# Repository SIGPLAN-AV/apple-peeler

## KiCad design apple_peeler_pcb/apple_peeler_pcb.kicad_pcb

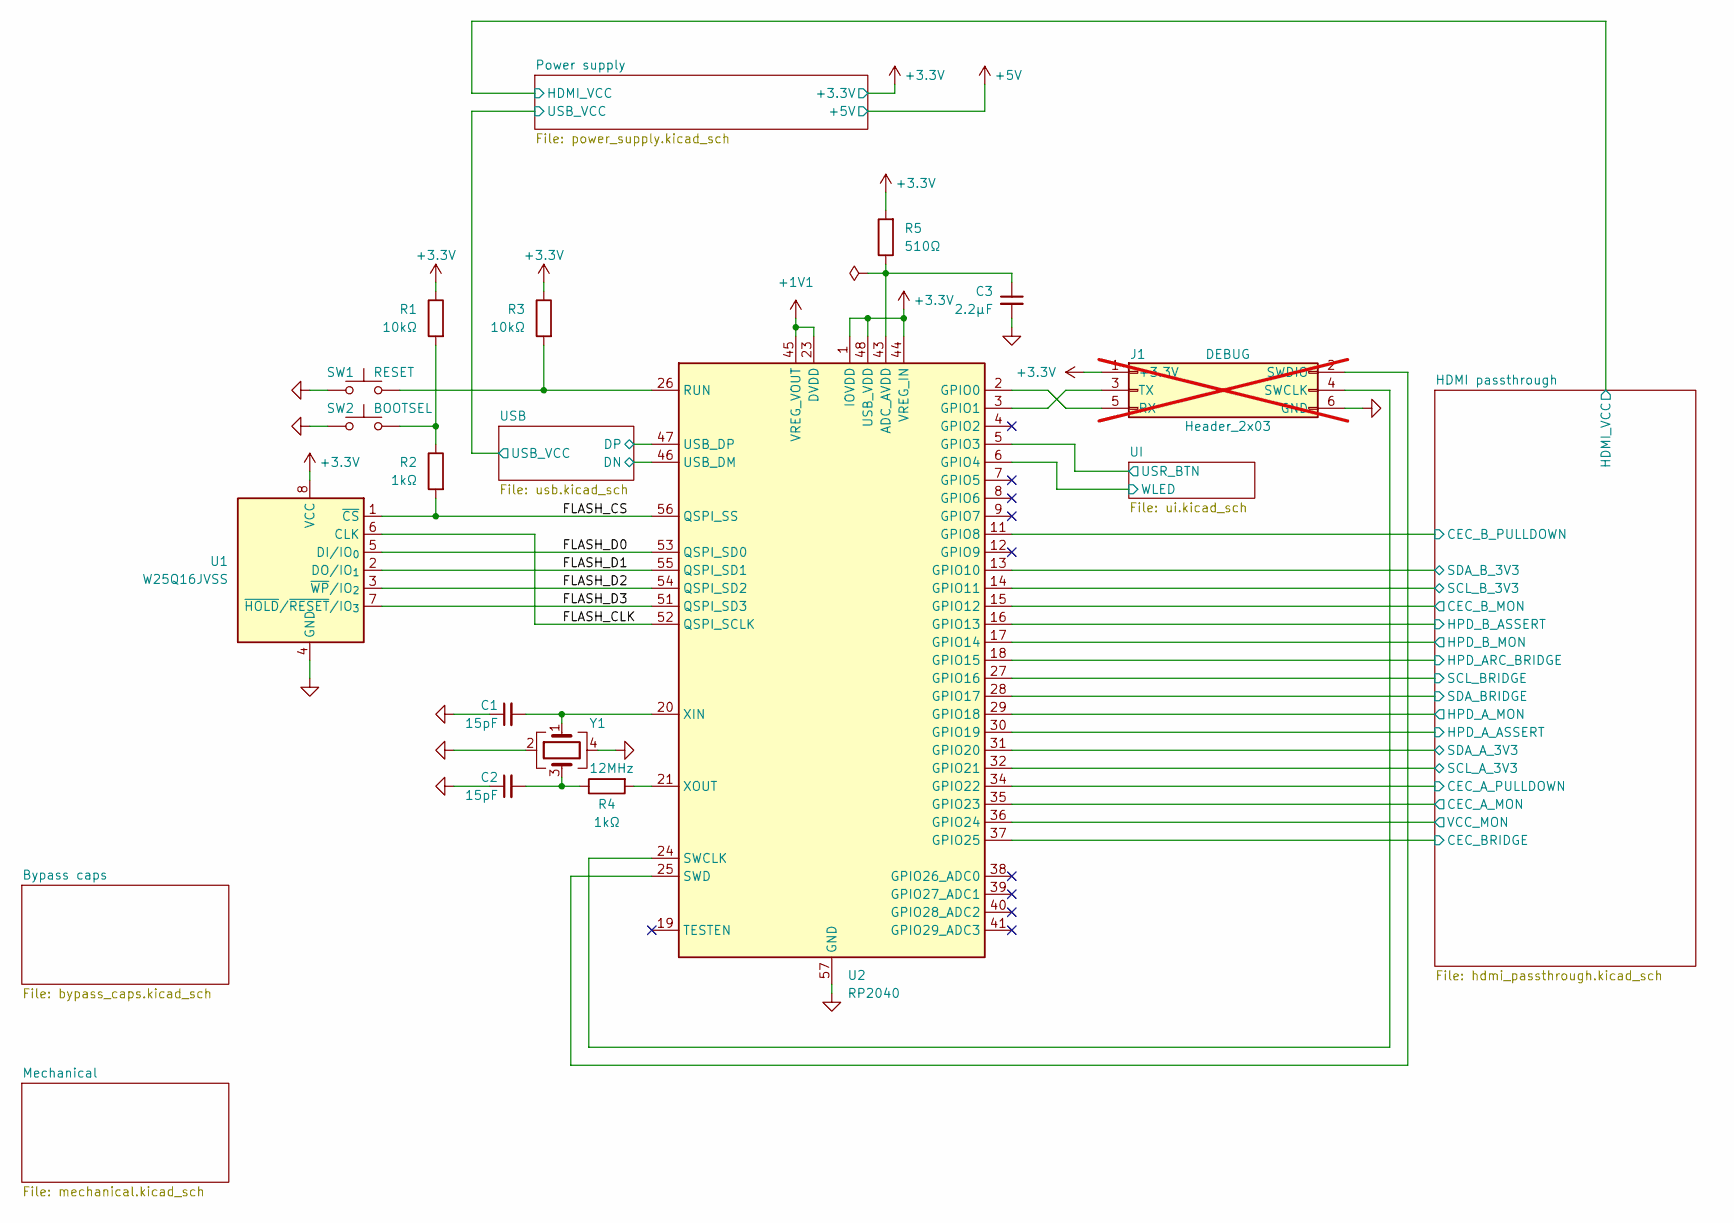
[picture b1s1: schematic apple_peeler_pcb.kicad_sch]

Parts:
C1, C2: 15pF; C_0805_2012Metric; MPN C 15pF 50V 0805; LCSC C107110
C3: 2.2μF; C_0805_2012Metric; MPN C 2.2μF 25V 0805; LCSC C377773
J1: Header_2x03; PinHeader_2x03_P2.54mm_Vertical; not fitted
R1, R3: 10kΩ; R_0805_2012Metric; MPN R 10kΩ 125mW 0805; LCSC C17414
R2, R4: 1kΩ; R_0805_2012Metric; MPN R 1kΩ 125mW 0805; LCSC C17513
R5: 510Ω; R_0805_2012Metric; MPN R 510Ω 125mW 0805; LCSC C17734
SW1, SW2: SPST BTN; SW_Push_1P1T_XKB_TS-1187A; MPN TS-1187A-B-A-B; LCSC C318884
U1: W25Q16JVSS; SOIC-8_5.3x5.3mm_P1.27mm; MPN W25Q16JVSSIQ; LCSC C131025
U2: RP2040; QFN-56-1EP_7x7mm_P0.4mm_EP3.2x3.2mm; MPN RP2040; LCSC C2040
Y1: 12MHz; Crystal_SMD_3225-4Pin_3.2x2.5mm; MPN X322512MSB4SI; LCSC C9002

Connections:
+1V1: U2.23 (DVDD), U2.45 (VREG_VOUT), U2.50 (DVDD); also elsewhere on the board
+3.3V: J1.1, R1.1, R3.1, R5.2, U1.8 (VCC), U2.1 (IOVDD), U2.10 (IOVDD), U2.22 (IOVDD), U2.33 (IOVDD), U2.42 (IOVDD), U2.44 (VREG_IN), U2.48 (USB_VDD), U2.49 (IOVDD); also elsewhere on the board
/FLASH_CLK: U1.6 (CLK), U2.52 (QSPI_SCLK)
/FLASH_CS: R2.2, U1.1 (~CS), U2.56 (QSPI_SS)
/FLASH_D0: U1.5 (DI/IO_{0}), U2.53 (QSPI_SD0)
/FLASH_D1: U1.2 (DO/IO_{1}), U2.55 (QSPI_SD1)
/FLASH_D2: U1.3 (~WP/IO_{2}), U2.54 (QSPI_SD2)
/FLASH_D3: U1.7 (~HOLD/~RESET/IO_{3}), U2.51 (QSPI_SD3)
/HDMI passthrough/CEC_A_MON: U2.35 (GPIO23); also elsewhere on the board
/HDMI passthrough/CEC_A_PULLDOWN: U2.34 (GPIO22); also elsewhere on the board
/HDMI passthrough/CEC_BRIDGE: U2.37 (GPIO25); also elsewhere on the board
/HDMI passthrough/CEC_B_MON: U2.15 (GPIO12); also elsewhere on the board
/HDMI passthrough/CEC_B_PULLDOWN: U2.11 (GPIO8); also elsewhere on the board
/HDMI passthrough/HPD_ARC_BRIDGE: U2.18 (GPIO15); also elsewhere on the board
/HDMI passthrough/HPD_A_ASSERT: U2.30 (GPIO19); also elsewhere on the board
/HDMI passthrough/HPD_A_MON: U2.29 (GPIO18); also elsewhere on the board
/HDMI passthrough/HPD_B_ASSERT: U2.16 (GPIO13); also elsewhere on the board
/HDMI passthrough/HPD_B_MON: U2.17 (GPIO14); also elsewhere on the board
/HDMI passthrough/SCL_A_3V3: U2.32 (GPIO21); also elsewhere on the board
/HDMI passthrough/SCL_BRIDGE: U2.27 (GPIO16); also elsewhere on the board
/HDMI passthrough/SCL_B_3V3: U2.14 (GPIO11); also elsewhere on the board
/HDMI passthrough/SDA_A_3V3: U2.31 (GPIO20); also elsewhere on the board
/HDMI passthrough/SDA_BRIDGE: U2.28 (GPIO17); also elsewhere on the board
/HDMI passthrough/SDA_B_3V3: U2.13 (GPIO10); also elsewhere on the board
/HDMI passthrough/VCC_MON: U2.36 (GPIO24); also elsewhere on the board
/UI/USR_BTN: U2.5 (GPIO3); also elsewhere on the board
/UI/WLED: U2.6 (GPIO4); also elsewhere on the board
/USB/DN: U2.46 (USB_DM); also elsewhere on the board
/USB/DP: U2.47 (USB_DP); also elsewhere on the board
GND: C1.1, C2.1, C3.2, J1.6, SW1.1, SW2.1, U1.4 (GND), U2.57 (GND), Y1.2, Y1.4; also elsewhere on the board
unnamed: C2.2, R4.1, Y1.3
unnamed: J1.2, U2.25 (SWD)
unnamed: J1.3, U2.3 (GPIO1)
unnamed: J1.4, U2.24 (SWCLK)
unnamed: J1.5, U2.2 (GPIO0)
unnamed: R1.2, R2.1, SW2.2
unnamed: C3.1, R5.1, U2.43 (ADC_AVDD)
unnamed: R3.2, SW1.2, U2.26 (RUN)
unnamed: C1.2, U2.20 (XIN), Y1.1
unnamed: R4.2, U2.21 (XOUT)

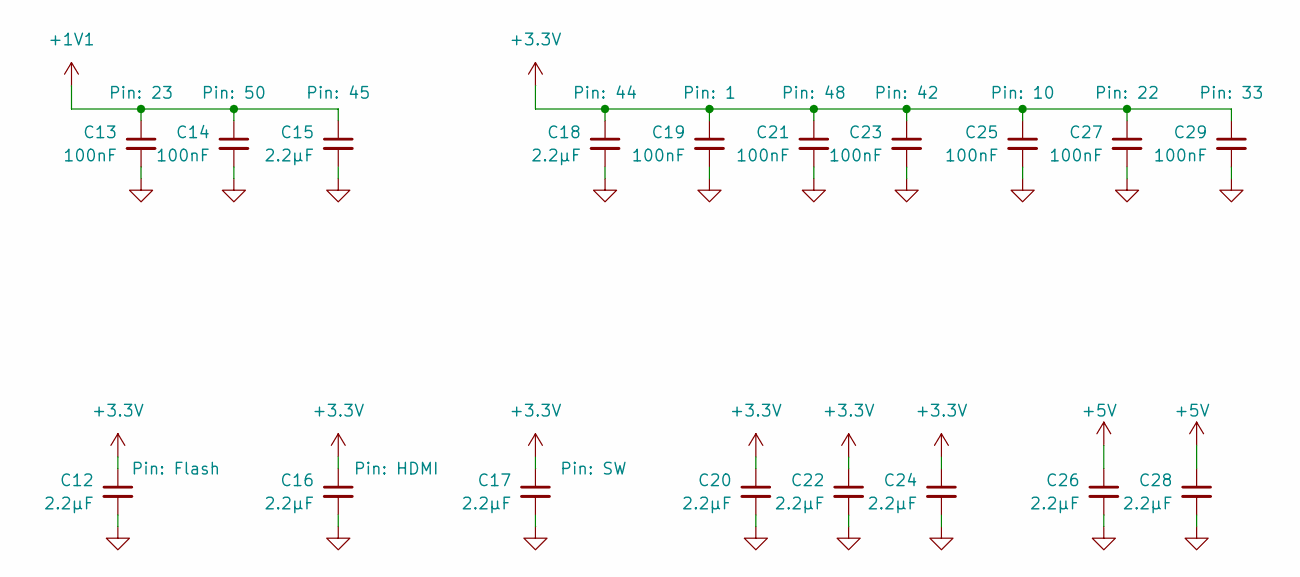
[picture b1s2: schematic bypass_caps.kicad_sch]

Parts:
C12, C15, C16, C17, C18, C20, C22, C24, C26, C28: 2.2μF; C_0805_2012Metric; MPN C 2.2μF 25V 0805; LCSC C377773
C13, C14, C19, C21, C23, C25, C27, C29: 100nF; C_0805_2012Metric; MPN C 100nF 50V 0805; LCSC C49678

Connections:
+1V1: C13.1, C14.1, C15.1; also elsewhere on the board
+3.3V: C12.1, C16.1, C17.1, C18.1, C19.1, C20.1, C21.1, C22.1, C23.1, C24.1, C25.1, C27.1, C29.1; also elsewhere on the board
+5V: C26.1, C28.1; also elsewhere on the board
GND: C12.2, C13.2, C14.2, C15.2, C16.2, C17.2, C18.2, C19.2, C20.2, C21.2, C22.2, C23.2, C24.2, C25.2, C26.2, C27.2, C28.2, C29.2; also elsewhere on the board

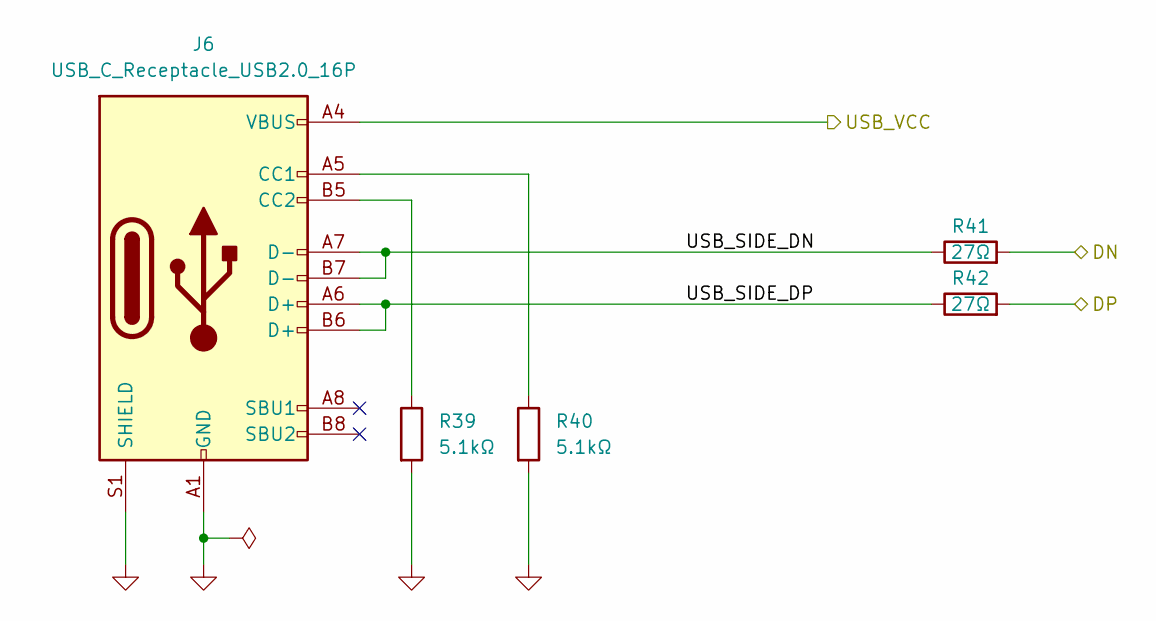
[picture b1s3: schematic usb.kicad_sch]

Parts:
J6: USB_C_Receptacle_USB2.0_16P; USB_C_Receptacle_G-Switch_GT-USB-7010ASV; MPN TYPE-C 16PIN 2MD(073); LCSC C2765186
R39, R40: 5.1kΩ; R_0805_2012Metric; MPN R 5.1kΩ 125mW 0805; LCSC C27834
R41, R42: 27Ω; R_0805_2012Metric; MPN R 27Ω 125mW 0805; LCSC C17594

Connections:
/Power supply/USB_VCC: J6.A4 (VBUS), J6.A9 (VBUS), J6.B4 (VBUS), J6.B9 (VBUS); also elsewhere on the board
/USB/DN: R41.2; also elsewhere on the board
/USB/DP: R42.2; also elsewhere on the board
/USB/USB_SIDE_DN: J6.A7 (D-), J6.B7 (D-), R41.1
/USB/USB_SIDE_DP: J6.A6 (D+), J6.B6 (D+), R42.1
GND: J6.A1 (GND), J6.A12 (GND), J6.B1 (GND), J6.B12 (GND), J6.S1 (SHIELD), R39.2, R40.2; also elsewhere on the board
unnamed: J6.A5 (CC1), R40.1
unnamed: J6.B5 (CC2), R39.1

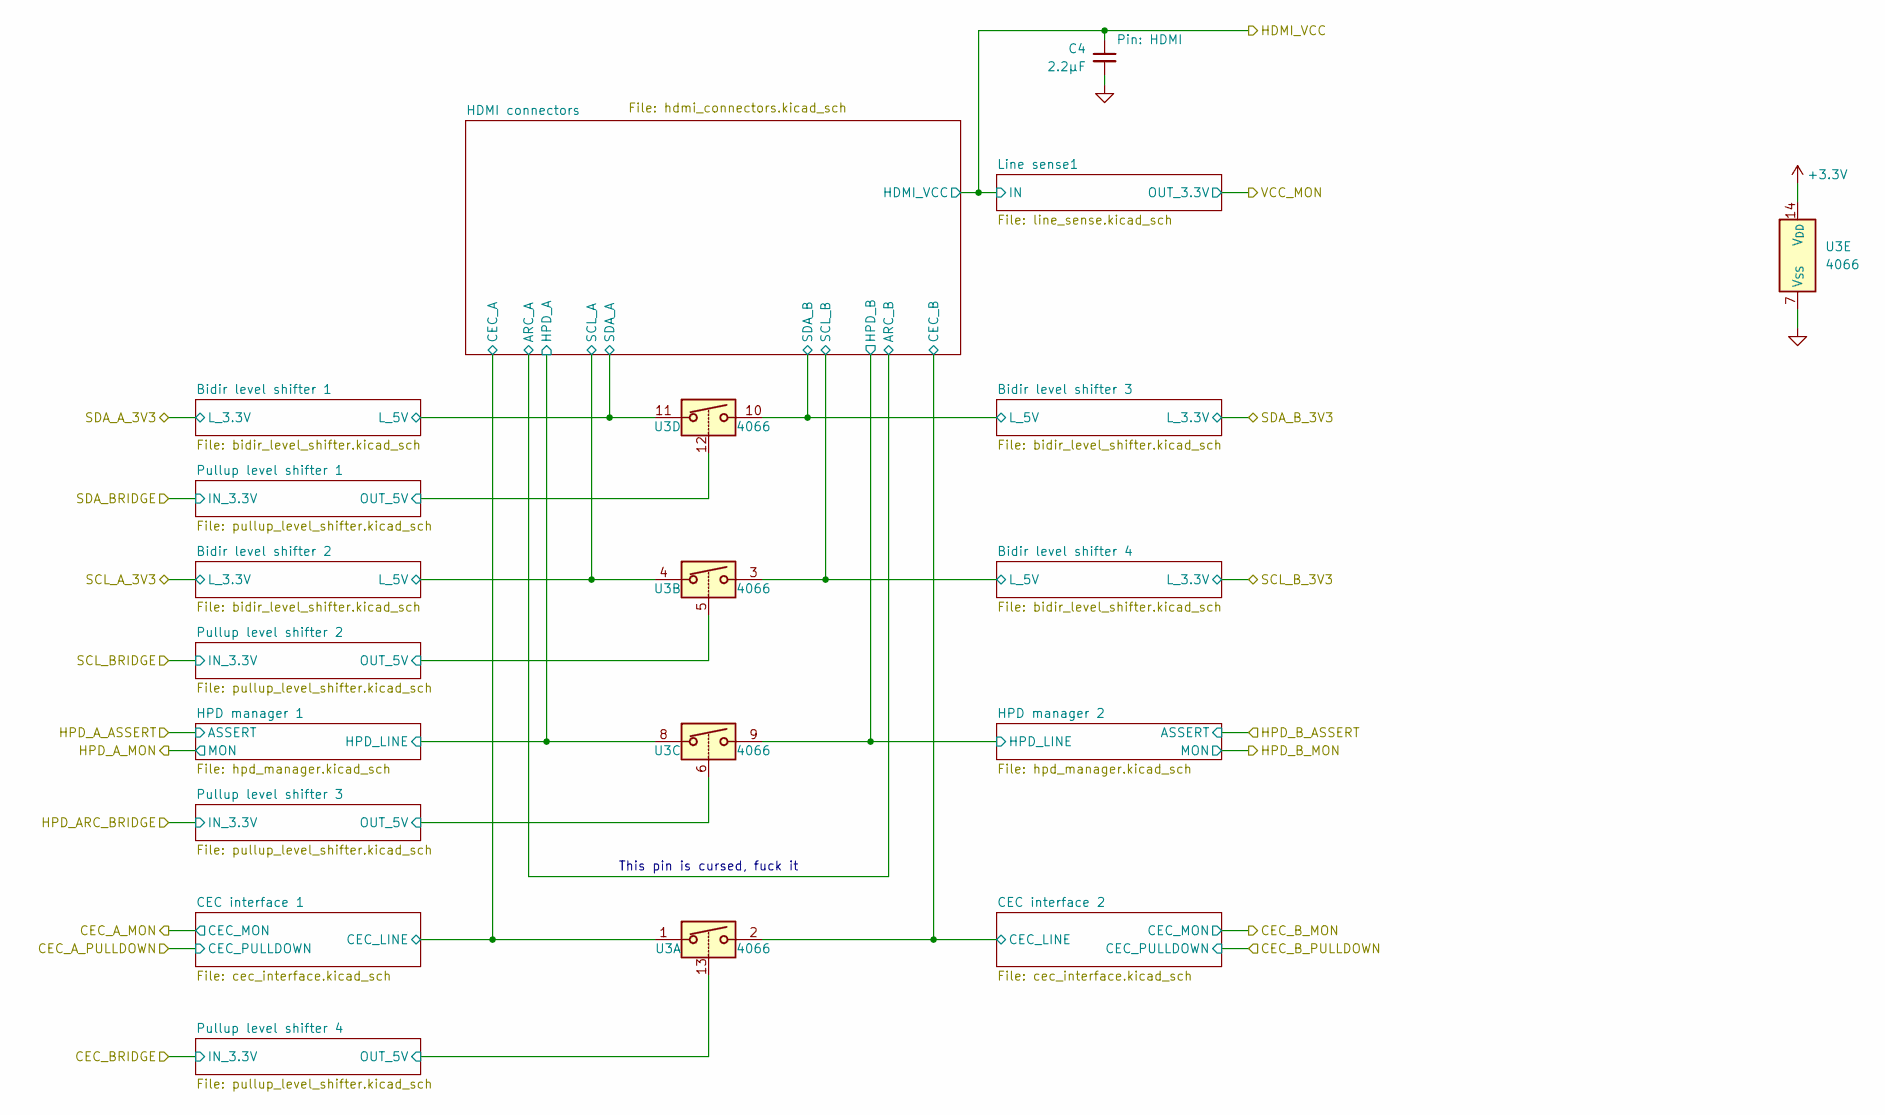
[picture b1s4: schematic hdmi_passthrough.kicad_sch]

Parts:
C4: 2.2μF; C_0805_2012Metric; MPN C 2.2μF 25V 0805; LCSC C377773
U3: 4066; SO-14_3.9x8.65mm_P1.27mm; MPN CD4066BM/TR; LCSC C512770

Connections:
+3.3V: U3.14 (V_{DD}); also elsewhere on the board
/HDMI passthrough/Bidir level shifter 1/L_5V: U3.11; also elsewhere on the board
/HDMI passthrough/Bidir level shifter 2/L_5V: U3.4; also elsewhere on the board
/HDMI passthrough/Bidir level shifter 3/L_5V: U3.10; also elsewhere on the board
/HDMI passthrough/Bidir level shifter 4/L_5V: U3.3; also elsewhere on the board
/HDMI passthrough/CEC interface 1/CEC_LINE: U3.1; also elsewhere on the board
/HDMI passthrough/CEC interface 2/CEC_LINE: U3.2; also elsewhere on the board
/HDMI passthrough/HDMI connectors/HPD_A: U3.8; also elsewhere on the board
/HDMI passthrough/HDMI connectors/HPD_B: U3.9; also elsewhere on the board
/HDMI passthrough/HDMI_VCC: C4.1; also elsewhere on the board
/HDMI passthrough/Pullup level shifter 1/OUT_5V: U3.12; also elsewhere on the board
/HDMI passthrough/Pullup level shifter 2/OUT_5V: U3.5; also elsewhere on the board
/HDMI passthrough/Pullup level shifter 3/OUT_5V: U3.6; also elsewhere on the board
/HDMI passthrough/Pullup level shifter 4/OUT_5V: U3.13; also elsewhere on the board
GND: C4.2, U3.7 (V_{SS}); also elsewhere on the board

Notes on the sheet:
This pin is cursed, fuck it

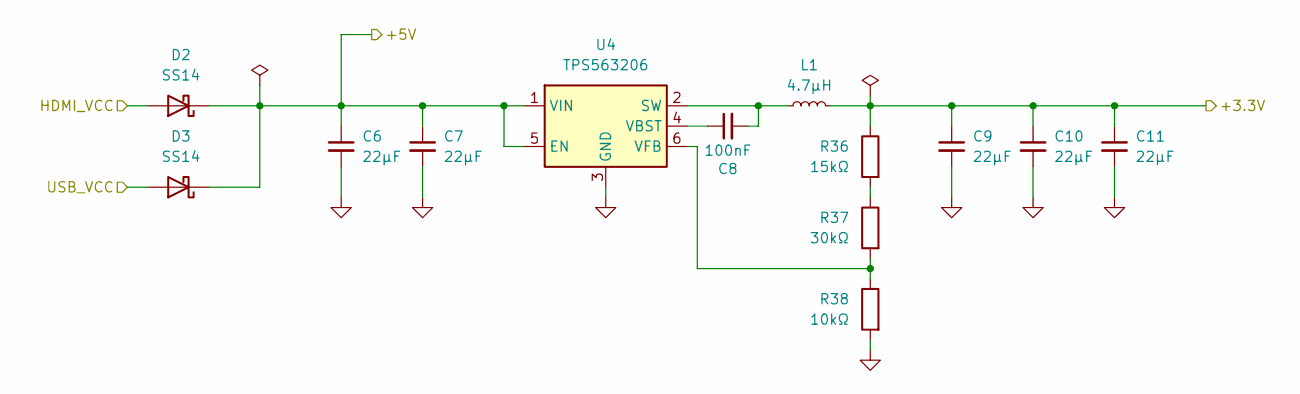
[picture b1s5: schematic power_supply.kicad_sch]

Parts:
C6, C7, C9, C10, C11: 22μF; C_0805_2012Metric; MPN C 22μF 25V 0805; LCSC C45783
C8: 100nF; C_0805_2012Metric; MPN C 100nF 50V 0805; LCSC C49678
D2, D3: SS14; D_SMA; MPN SS14; LCSC C2480
L1: 4.7μH; L_Sunlord_SWPA5020S; MPN SWPA5020S4R7MT; LCSC C43183
R36: 15kΩ; R_0805_2012Metric; MPN R 15kΩ 125mW 0805; LCSC C17475
R37: 30kΩ; R_0805_2012Metric; MPN R 30kΩ 125mW 0805; LCSC C17621
R38: 10kΩ; R_0805_2012Metric; MPN R 10kΩ 125mW 0805; LCSC C17414
U4: TPS563206; SOT-563; MPN TPS563206DRLR; LCSC C22427434

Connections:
+3.3V: C9.1, C10.1, C11.1, L1.2, R36.1; also elsewhere on the board
+5V: C6.1, C7.1, D2.1 (K), D3.1 (K), U4.1 (VIN), U4.5 (EN); also elsewhere on the board
/HDMI passthrough/HDMI_VCC: D2.2 (A); also elsewhere on the board
/Power supply/USB_VCC: D3.2 (A); also elsewhere on the board
GND: C6.2, C7.2, C9.2, C10.2, C11.2, R38.2, U4.3 (GND); also elsewhere on the board
unnamed: R36.2, R37.1
unnamed: C8.2, L1.1, U4.2 (SW)
unnamed: C8.1, U4.4 (VBST)
unnamed: R37.2, R38.1, U4.6 (VFB)

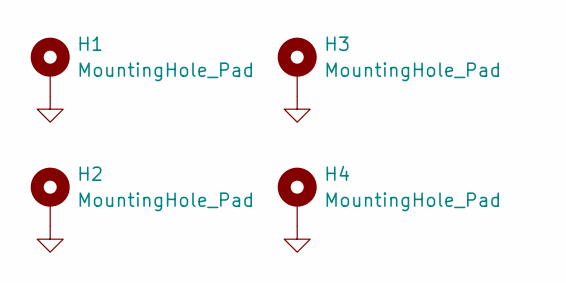
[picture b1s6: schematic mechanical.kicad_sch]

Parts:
H1, H2, H3, H4: MountingHole_Pad; MountingHole_3.2mm_M3_Pad_Via

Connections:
GND: H1.1, H2.1, H3.1, H4.1; also elsewhere on the board

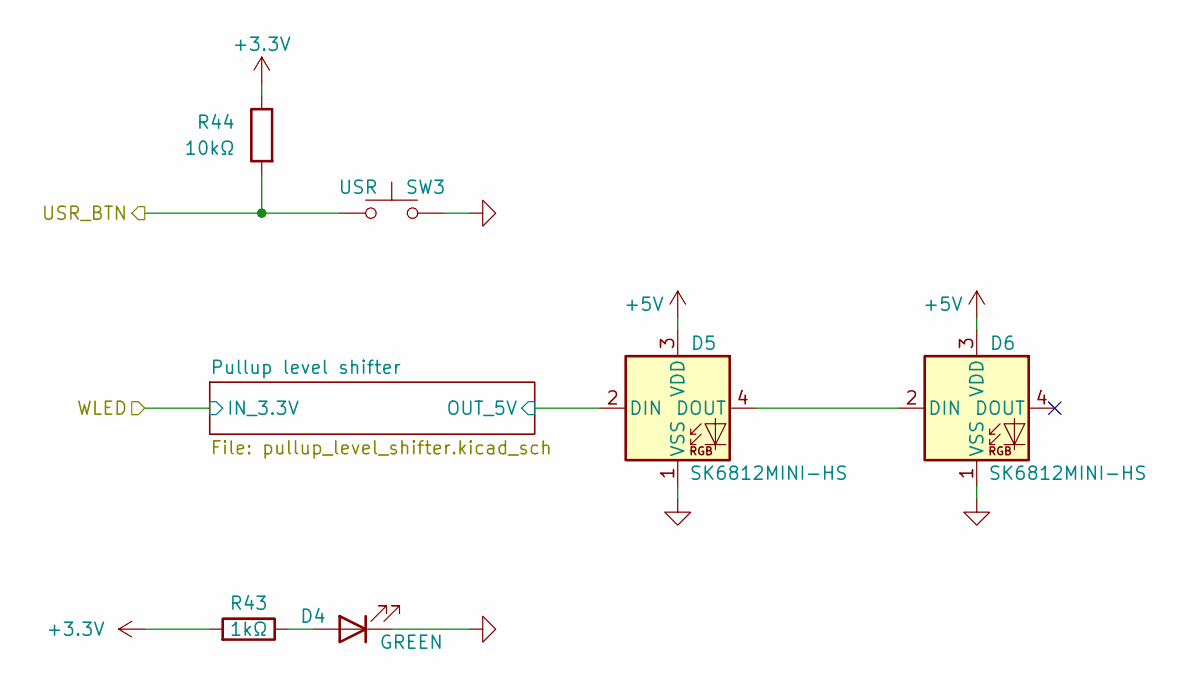
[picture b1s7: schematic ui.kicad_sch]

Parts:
D4: GREEN; LED_0805_2012Metric; MPN KT-0805G; LCSC C2297
D5, D6: SK6812MINI-HS; LED_SK6812MINI_HS_012; MPN SK6812MINI-HS; LCSC C2922787
R43: 1kΩ; R_0805_2012Metric; MPN R 1kΩ 125mW 0805; LCSC C17513
R44: 10kΩ; R_0805_2012Metric; MPN R 10kΩ 125mW 0805; LCSC C17414
SW3: SPST BTN; SW_Push_1P1T_XKB_TS-1187A; MPN TS-1187A-B-A-B; LCSC C318884

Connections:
+3.3V: R43.2, R44.1; also elsewhere on the board
+5V: D5.3 (VDD), D6.3 (VDD); also elsewhere on the board
/UI/Pullup level shifter/OUT_5V: D5.2 (DIN); also elsewhere on the board
/UI/USR_BTN: R44.2, SW3.2; also elsewhere on the board
GND: D4.1 (K), D5.1 (VSS), D6.1 (VSS), SW3.1; also elsewhere on the board
unnamed: D4.2 (A), R43.1
unnamed: D5.4 (DOUT), D6.2 (DIN)

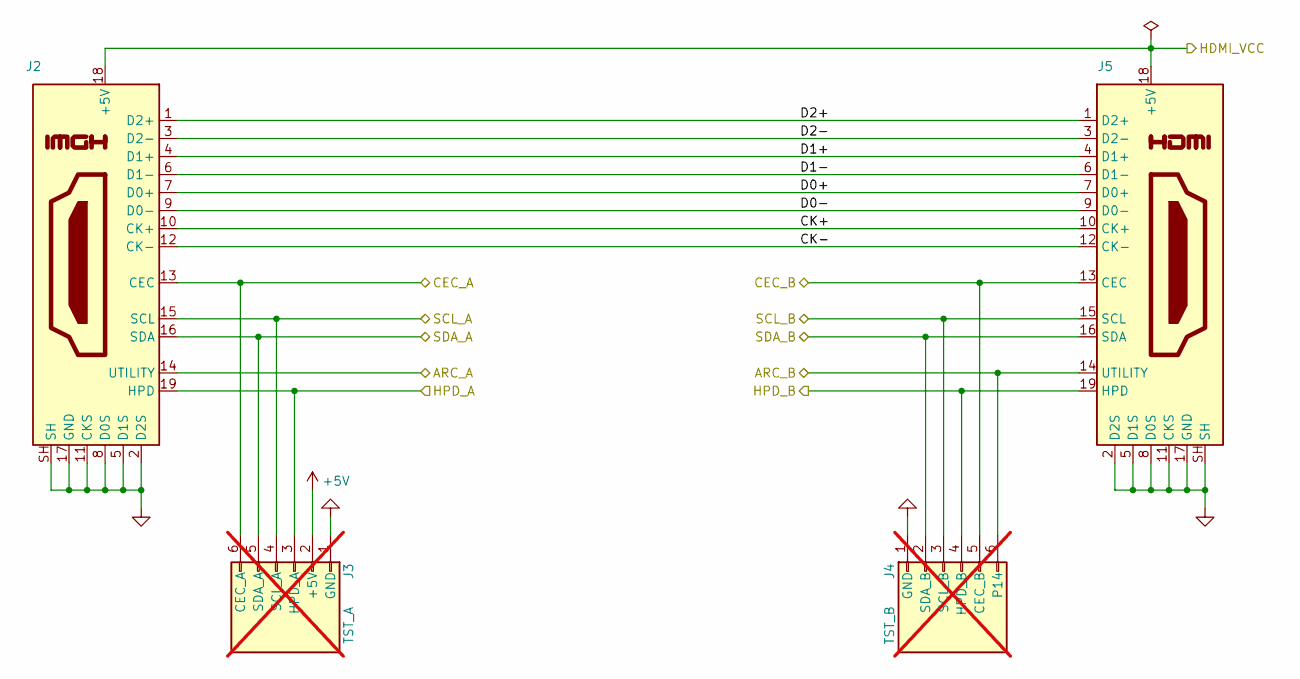
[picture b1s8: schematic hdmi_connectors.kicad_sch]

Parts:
J2, J5: HDMI-001 19PCBTP; HDMI_A_Molex_208658-1001_Horizontal; MPN Molex_208658; LCSC C138388
J3, J4: Header_01x06; PinHeader_1x06_P2.54mm_Vertical; MPN Header_01x06; not fitted

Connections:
+5V: J3.2; also elsewhere on the board
/HDMI passthrough/Bidir level shifter 1/L_5V: J2.16 (SDA), J3.5; also elsewhere on the board
/HDMI passthrough/Bidir level shifter 2/L_5V: J2.15 (SCL), J3.4; also elsewhere on the board
/HDMI passthrough/Bidir level shifter 3/L_5V: J4.2, J5.16 (SDA); also elsewhere on the board
/HDMI passthrough/Bidir level shifter 4/L_5V: J4.3, J5.15 (SCL); also elsewhere on the board
/HDMI passthrough/CEC interface 1/CEC_LINE: J2.13 (CEC), J3.6; also elsewhere on the board
/HDMI passthrough/CEC interface 2/CEC_LINE: J4.5, J5.13 (CEC); also elsewhere on the board
/HDMI passthrough/HDMI connectors/ARC_A: J2.14 (UTILITY), J4.6, J5.14 (UTILITY)
/HDMI passthrough/HDMI connectors/CK+: J2.10 (CK+), J5.10 (CK+)
/HDMI passthrough/HDMI connectors/CK-: J2.12 (CK-), J5.12 (CK-)
/HDMI passthrough/HDMI connectors/D0+: J2.7 (D0+), J5.7 (D0+)
/HDMI passthrough/HDMI connectors/D0-: J2.9 (D0-), J5.9 (D0-)
/HDMI passthrough/HDMI connectors/D1+: J2.4 (D1+), J5.4 (D1+)
/HDMI passthrough/HDMI connectors/D1-: J2.6 (D1-), J5.6 (D1-)
/HDMI passthrough/HDMI connectors/D2+: J2.1 (D2+), J5.1 (D2+)
/HDMI passthrough/HDMI connectors/D2-: J2.3 (D2-), J5.3 (D2-)
/HDMI passthrough/HDMI connectors/HPD_A: J2.19 (HPD), J3.3; also elsewhere on the board
/HDMI passthrough/HDMI connectors/HPD_B: J4.4, J5.19 (HPD); also elsewhere on the board
/HDMI passthrough/HDMI_VCC: J2.18 (+5V), J5.18 (+5V); also elsewhere on the board
GND: J2.2 (D2S), J2.5 (D1S), J2.8 (D0S), J2.11 (CKS), J2.17 (GND), J2.SH, J3.1, J4.1, J5.2 (D2S), J5.5 (D1S), J5.8 (D0S), J5.11 (CKS), J5.17 (GND), J5.SH; also elsewhere on the board

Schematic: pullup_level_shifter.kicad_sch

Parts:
Q5: 2N7002; SOT-23; MPN 2N7002; LCSC C8545
R14: 510Ω; R_0805_2012Metric; MPN R 510Ω 125mW 0805; LCSC C17734
R15: 470kΩ; R_0805_2012Metric; MPN R 470kΩ 125mW 0805; LCSC C17709
R16: 10kΩ; R_0805_2012Metric; MPN R 10kΩ 125mW 0805; LCSC C17414

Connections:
+5V: R16.1; also elsewhere on the board
/HDMI passthrough/Pullup level shifter 1/OUT_5V: Q5.3 (D), R16.2; also elsewhere on the board
/HDMI passthrough/SDA_BRIDGE: R14.1; also elsewhere on the board
GND: Q5.2 (S), R15.2; also elsewhere on the board
unnamed: Q5.1 (G), R14.2, R15.1

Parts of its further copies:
Q6, Q7, Q10, Q18: 2N7002; SOT-23; MPN 2N7002; LCSC C8545
R17, R20, R29, R62: 510Ω; R_0805_2012Metric; MPN R 510Ω 125mW 0805; LCSC C17734
R18, R21, R30, R63: 470kΩ; R_0805_2012Metric; MPN R 470kΩ 125mW 0805; LCSC C17709
R19, R22, R31, R64: 10kΩ; R_0805_2012Metric; MPN R 10kΩ 125mW 0805; LCSC C17414

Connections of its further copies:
+5V: R19.1, R22.1, R31.1, R64.1; also elsewhere on the board
/HDMI passthrough/CEC_BRIDGE: R29.1; also elsewhere on the board
/HDMI passthrough/HPD_ARC_BRIDGE: R20.1; also elsewhere on the board
/HDMI passthrough/Pullup level shifter 2/OUT_5V: Q6.3 (D), R19.2; also elsewhere on the board
/HDMI passthrough/Pullup level shifter 3/OUT_5V: Q7.3 (D), R22.2; also elsewhere on the board
/HDMI passthrough/Pullup level shifter 4/OUT_5V: Q10.3 (D), R31.2; also elsewhere on the board
/HDMI passthrough/SCL_BRIDGE: R17.1; also elsewhere on the board
/UI/Pullup level shifter/OUT_5V: Q18.3 (D), R64.2; also elsewhere on the board
/UI/WLED: R62.1; also elsewhere on the board
GND: Q6.2 (S), Q7.2 (S), Q10.2 (S), Q18.2 (S), R18.2, R21.2, R30.2, R63.2; also elsewhere on the board
unnamed: Q6.1 (G), R17.2, R18.1
unnamed: Q7.1 (G), R20.2, R21.1
unnamed: Q10.1 (G), R29.2, R30.1
unnamed: Q18.1 (G), R62.2, R63.1

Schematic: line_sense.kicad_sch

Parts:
Q8: 2N7002; SOT-23; MPN 2N7002; LCSC C8545
R23: 510Ω; R_0805_2012Metric; MPN R 510Ω 125mW 0805; LCSC C17734
R24: 470kΩ; R_0805_2012Metric; MPN R 470kΩ 125mW 0805; LCSC C17709
R25: 10kΩ; R_0805_2012Metric; MPN R 10kΩ 125mW 0805; LCSC C17414

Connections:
+3.3V: R25.1; also elsewhere on the board
/HDMI passthrough/HDMI connectors/HPD_B: R23.1; also elsewhere on the board
/HDMI passthrough/HPD_B_MON: Q8.3 (D), R25.2; also elsewhere on the board
GND: Q8.2 (S), R24.2; also elsewhere on the board
unnamed: Q8.1 (G), R23.2, R24.1

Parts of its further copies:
Q9, Q12: 2N7002; SOT-23; MPN 2N7002; LCSC C8545
R26, R45: 510Ω; R_0805_2012Metric; MPN R 510Ω 125mW 0805; LCSC C17734
R27, R46: 470kΩ; R_0805_2012Metric; MPN R 470kΩ 125mW 0805; LCSC C17709
R28, R47: 10kΩ; R_0805_2012Metric; MPN R 10kΩ 125mW 0805; LCSC C17414

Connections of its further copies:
+3.3V: R28.1, R47.1; also elsewhere on the board
/HDMI passthrough/HDMI connectors/HPD_A: R45.1; also elsewhere on the board
/HDMI passthrough/HDMI_VCC: R26.1; also elsewhere on the board
/HDMI passthrough/HPD_A_MON: Q12.3 (D), R47.2; also elsewhere on the board
/HDMI passthrough/VCC_MON: Q9.3 (D), R28.2; also elsewhere on the board
GND: Q9.2 (S), Q12.2 (S), R27.2, R46.2; also elsewhere on the board
unnamed: Q9.1 (G), R26.2, R27.1
unnamed: Q12.1 (G), R45.2, R46.1

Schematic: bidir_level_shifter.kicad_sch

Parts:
Q1: 2N7002; SOT-23; MPN 2N7002; LCSC C8545
R6, R7: 10kΩ; R_0805_2012Metric; MPN R 10kΩ 125mW 0805; LCSC C17414

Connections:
+3.3V: Q1.1 (G), R6.1; also elsewhere on the board
+5V: R7.1; also elsewhere on the board
/HDMI passthrough/Bidir level shifter 1/L_5V: Q1.3 (D), R7.2; also elsewhere on the board
/HDMI passthrough/SDA_A_3V3: Q1.2 (S), R6.2; also elsewhere on the board

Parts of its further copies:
Q2, Q3, Q4: 2N7002; SOT-23; MPN 2N7002; LCSC C8545
R8, R9, R10, R11, R12, R13: 10kΩ; R_0805_2012Metric; MPN R 10kΩ 125mW 0805; LCSC C17414

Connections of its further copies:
+3.3V: Q2.1 (G), Q3.1 (G), Q4.1 (G), R8.1, R10.1, R12.1; also elsewhere on the board
+5V: R9.1, R11.1, R13.1; also elsewhere on the board
/HDMI passthrough/Bidir level shifter 2/L_5V: Q2.3 (D), R9.2; also elsewhere on the board
/HDMI passthrough/Bidir level shifter 3/L_5V: Q3.3 (D), R11.2; also elsewhere on the board
/HDMI passthrough/Bidir level shifter 4/L_5V: Q4.3 (D), R13.2; also elsewhere on the board
/HDMI passthrough/SCL_A_3V3: Q2.2 (S), R8.2; also elsewhere on the board
/HDMI passthrough/SCL_B_3V3: Q4.2 (S), R12.2; also elsewhere on the board
/HDMI passthrough/SDA_B_3V3: Q3.2 (S), R10.2; also elsewhere on the board

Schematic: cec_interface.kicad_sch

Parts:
C5: 100pF; C_0805_2012Metric; MPN C 100pF 50V 0805; LCSC C1790
D1: 1N4148WS; D_SOD-323; MPN 1N4148WS; LCSC C2128
Q11: 2N7002; SOT-23; MPN 2N7002; LCSC C8545
R32: 510Ω; R_0805_2012Metric; MPN R 510Ω 125mW 0805; LCSC C17734
R33: 470kΩ; R_0805_2012Metric; MPN R 470kΩ 125mW 0805; LCSC C17709
R34: 27kΩ; R_0805_2012Metric; MPN R 27kΩ 125mW 0805; LCSC C17593
R35: 47kΩ; R_0805_2012Metric; MPN R 47kΩ 125mW 0805; LCSC C17713

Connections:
+3.3V: R34.1; also elsewhere on the board
/HDMI passthrough/CEC interface 1/CEC_LINE: D1.1 (K), Q11.3 (D); also elsewhere on the board
/HDMI passthrough/CEC_A_MON: C5.1, R35.2; also elsewhere on the board
/HDMI passthrough/CEC_A_PULLDOWN: R32.1; also elsewhere on the board
GND: C5.2, Q11.2 (S), R33.2; also elsewhere on the board
unnamed: D1.2 (A), R34.2, R35.1
unnamed: Q11.1 (G), R32.2, R33.1

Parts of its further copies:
C30: 100pF; C_0805_2012Metric; MPN C 100pF 50V 0805; LCSC C1790
D7: 1N4148WS; D_SOD-323; MPN 1N4148WS; LCSC C2128
Q17: 2N7002; SOT-23; MPN 2N7002; LCSC C8545
R58: 510Ω; R_0805_2012Metric; MPN R 510Ω 125mW 0805; LCSC C17734
R59: 470kΩ; R_0805_2012Metric; MPN R 470kΩ 125mW 0805; LCSC C17709
R60: 27kΩ; R_0805_2012Metric; MPN R 27kΩ 125mW 0805; LCSC C17593
R61: 47kΩ; R_0805_2012Metric; MPN R 47kΩ 125mW 0805; LCSC C17713

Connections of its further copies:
+3.3V: R60.1; also elsewhere on the board
/HDMI passthrough/CEC interface 2/CEC_LINE: D7.1 (K), Q17.3 (D); also elsewhere on the board
/HDMI passthrough/CEC_B_MON: C30.1, R61.2; also elsewhere on the board
/HDMI passthrough/CEC_B_PULLDOWN: R58.1; also elsewhere on the board
GND: C30.2, Q17.2 (S), R59.2; also elsewhere on the board
unnamed: D7.2 (A), R60.2, R61.1
unnamed: Q17.1 (G), R58.2, R59.1

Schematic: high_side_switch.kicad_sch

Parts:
Q13: 2N7002; SOT-23; MPN 2N7002; LCSC C8545
Q14: AO3401A; SOT-23; MPN AO3401A; LCSC C15127
R48, R51: 510Ω; R_0805_2012Metric; MPN R 510Ω 125mW 0805; LCSC C17734
R49, R52: 470kΩ; R_0805_2012Metric; MPN R 470kΩ 125mW 0805; LCSC C17709
R50: 10kΩ; R_0805_2012Metric; MPN R 10kΩ 125mW 0805; LCSC C17414

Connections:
+5V: Q14.2 (S), R50.1; also elsewhere on the board
/HDMI passthrough/HDMI connectors/HPD_A: Q14.3 (D), R52.1; also elsewhere on the board
/HDMI passthrough/HPD_A_ASSERT: R48.1; also elsewhere on the board
GND: Q13.2 (S), R49.2, R52.2; also elsewhere on the board
unnamed: Q13.3 (D), R51.2
unnamed: Q13.1 (G), R48.2, R49.1
unnamed: Q14.1 (G), R50.2, R51.1

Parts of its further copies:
Q15: 2N7002; SOT-23; MPN 2N7002; LCSC C8545
Q16: AO3401A; SOT-23; MPN AO3401A; LCSC C15127
R53, R56: 510Ω; R_0805_2012Metric; MPN R 510Ω 125mW 0805; LCSC C17734
R54, R57: 470kΩ; R_0805_2012Metric; MPN R 470kΩ 125mW 0805; LCSC C17709
R55: 10kΩ; R_0805_2012Metric; MPN R 10kΩ 125mW 0805; LCSC C17414

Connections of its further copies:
+5V: Q16.2 (S), R55.1; also elsewhere on the board
/HDMI passthrough/HDMI connectors/HPD_B: Q16.3 (D), R57.1; also elsewhere on the board
/HDMI passthrough/HPD_B_ASSERT: R53.1; also elsewhere on the board
GND: Q15.2 (S), R54.2, R57.2; also elsewhere on the board
unnamed: Q15.3 (D), R56.2
unnamed: Q15.1 (G), R53.2, R54.1
unnamed: Q16.1 (G), R55.2, R56.1

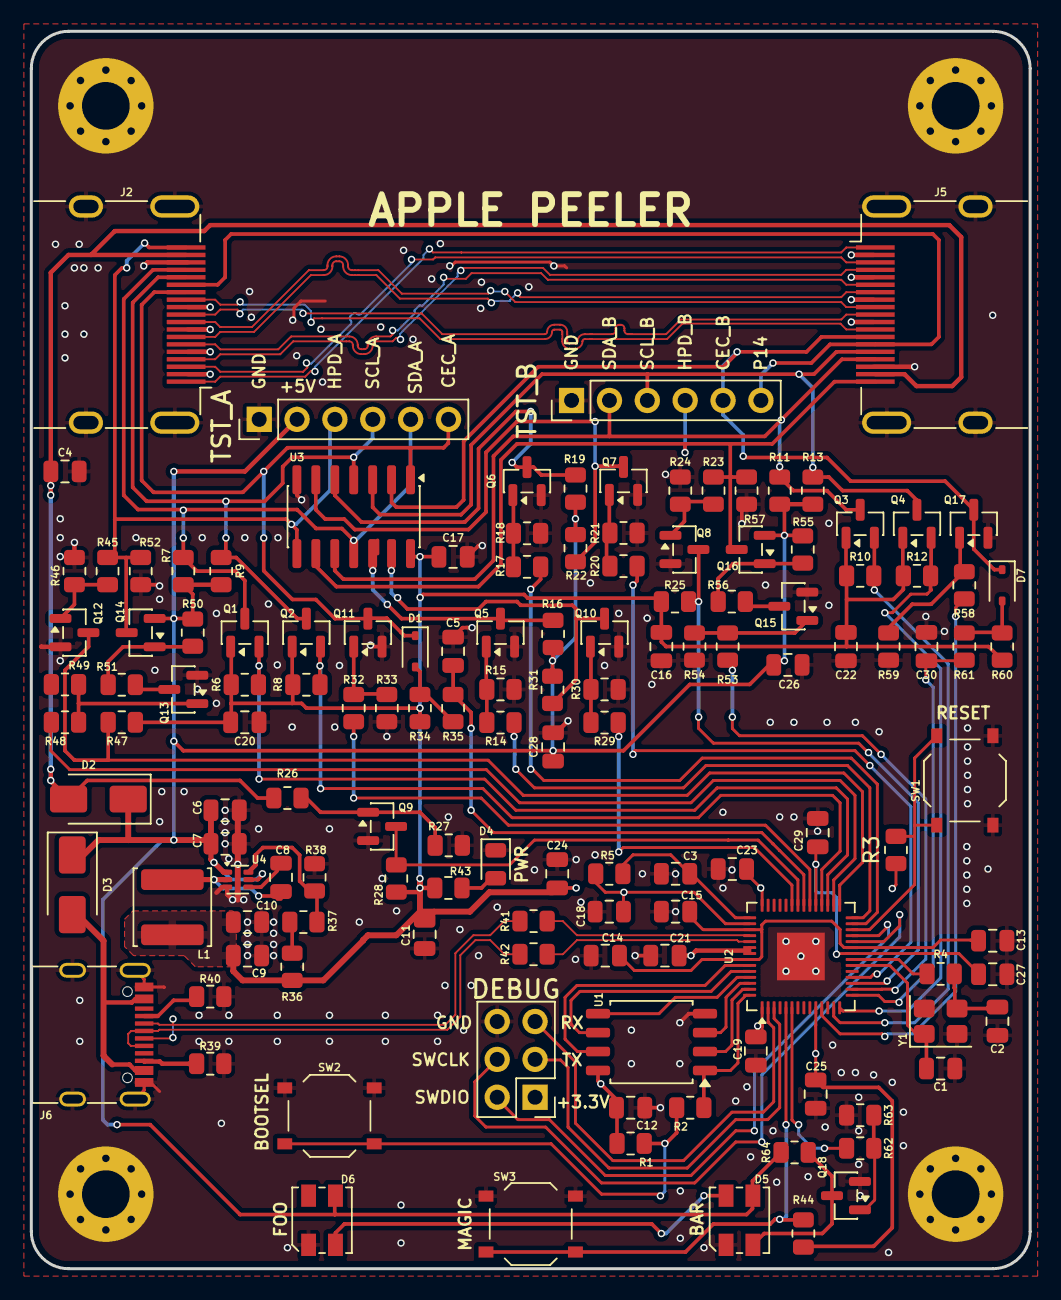
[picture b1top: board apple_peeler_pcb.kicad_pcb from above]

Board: 4 copper layers, 67.0 x 83.0 mm, 138 parts (0 on the bottom side), 93 nets.

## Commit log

2025-08-14 initial
2025-08-14 schematic and component assignments
2025-08-14 add some leds
2025-08-14 add power led
2025-08-14 we paid for all the pins, we're gonna use all the pins
2025-08-24 use wleds instead of individual leds
2025-08-25 some progress
2025-09-04 route and place MCU peripherals and power train
2025-09-04 route hdmi traces
2025-09-04 route side A level shifters
2025-09-04 cec interface A
2025-09-04 AAAAAAAAAAAAAAAAAAAAAAAAAAAAAAAAAAAAAAAAAAAAAAAAAAA
2025-09-04 passthrough switch level shifters
2025-09-04 make space for bypass cap near switch chip
2025-09-04 reannotate schematic
2025-09-05 route HPD B
2025-09-05 half-a-cec
2025-09-05 final level shifter
2025-09-07 sane names for subsheets
2025-09-07 vcc mon level shifter
2025-09-07 rg | xargs sed goes brrr
2025-09-08 add loads of test points
2025-09-08 route all power traces
2025-09-08 fuuuuuuuuuuuuck, I forgot the mounting holes
2025-09-08 attempt 1 of final arrangement
2025-09-08 all components placed inside board
2025-09-08 route all the rp2040 pins
2025-09-08 giant "SPAV"
2025-09-08 nicely-rounded corners
2025-09-08 copper seems done, only thing left is the silkscreen
2025-09-08 silkscreen inspect profile
2025-09-08 some silkscreen
2025-09-11 4L stackup, reroute +3.3V around rp2040
2025-09-13 completely destroy the SMPS routing
2025-09-14 reroute SMPS layout by closely following datasheet
2025-09-14 literally HDMI bloodbath
2025-09-14 fix connector labels and misc silkscreen
2025-09-14 jlcpbc drc
2025-09-14 woopsie
2025-09-14 fix clearance-related DRC and "fix" silkscreen-related DRC
2025-09-15 some final touches to HDMI layout
2025-09-17 change HDMI connector to one that's in stock
2025-09-17 add JLC order number label
2025-09-17 update SMPS inductor and divider
2025-09-17 correct inductor for smps
2025-09-17 prepare for fab
2025-09-22 replace fancy debug connectors by pin header to save $8
2025-09-22 poly
2025-09-22 remove orphaned vias
2025-09-26 FUCKING HELL why is the kicad library symbol wrong
    fix the pin order of rgb led symbol
2025-11-04 fix the fucking fucked D+ and D- lines
2025-11-04 fix the fucking WLED footprints
2025-11-04 add comment
